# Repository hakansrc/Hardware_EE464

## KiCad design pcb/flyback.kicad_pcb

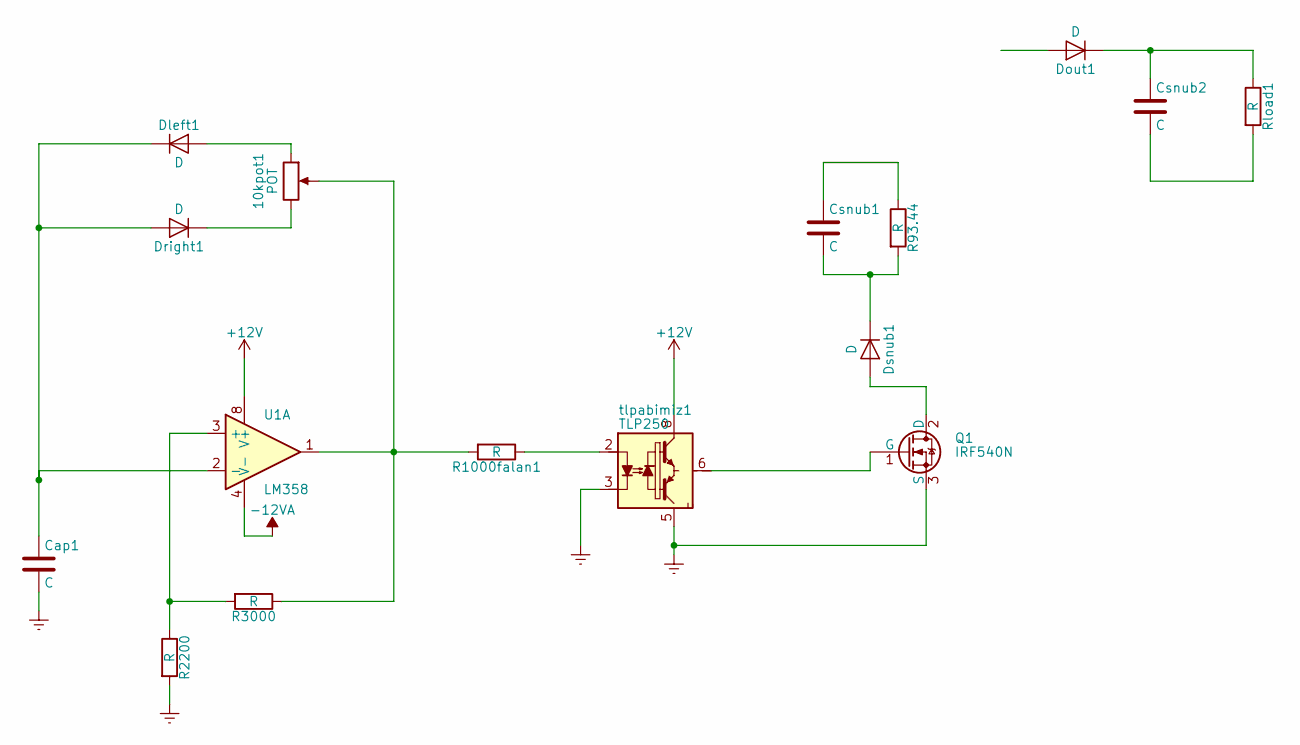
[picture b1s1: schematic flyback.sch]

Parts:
10kpot1: POT; Potentiometer_Alps_RK163_Single_Vertical
Cap1: C; C_Rect_L9.0mm_W2.5mm_P7.50mm_MKT
Csnub1: C; CP_Radial_D7.5mm_P2.50mm
Csnub2: C; CP_Radial_D26.0mm_P10.00mm_SnapIn
Dleft1: D; D_DO-201AD_P12.70mm_Horizontal
Dout1: D; D_5KPW_P12.70mm_Horizontal
Dright1: D; D_DO-201AD_P12.70mm_Horizontal
Dsnub1: D; D_A-405_P12.70mm_Horizontal
Q1: IRF540N; TO-220-3_Vertical
R93.44: R; R_Axial_Power_L38.0mm_W9.0mm_P45.72mm
R1000falan1, R2200, R3000: R; R_Axial_DIN0414_L11.9mm_D4.5mm_P15.24mm_Horizontal
Rload1: R; R_Axial_DIN0414_L11.9mm_D4.5mm_P15.24mm_Horizontal
U1: LM358; DIP-8_W8.89mm_SMDSocket_LongPads
tlpabimiz1: TLP250; DIP-8_W8.89mm_SMDSocket_LongPads

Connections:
+12V: U1.8 (V+), tlpabimiz1.8 (VCC)
-12VA: U1.4 (V-)
Earth: Cap1.2, Q1.3 (S), R2200.2, tlpabimiz1.3 (C), tlpabimiz1.5 (VEE)
unnamed: 10kpot1.1, Dleft1.2 (A)
unnamed: 10kpot1.2, R1000falan1.2, R3000.1, U1.1
unnamed: 10kpot1.3, Dright1.1 (K)
unnamed: Cap1.1, Dleft1.1 (K), Dright1.2 (A), U1.2 (-)
unnamed: Csnub1.1, R93.44.1
unnamed: Csnub1.2, Dsnub1.1 (K), R93.44.2
unnamed: Csnub2.1, Dout1.1 (K), Rload1.1
unnamed: Csnub2.2, Rload1.2
unnamed: Dsnub1.2 (A), Q1.2 (D)
unnamed: Q1.1 (G), tlpabimiz1.6 (VO), tlpabimiz1.7 (VO)
unnamed: R1000falan1.1, tlpabimiz1.2 (A)
unnamed: R2200.1, R3000.2, U1.3 (+)

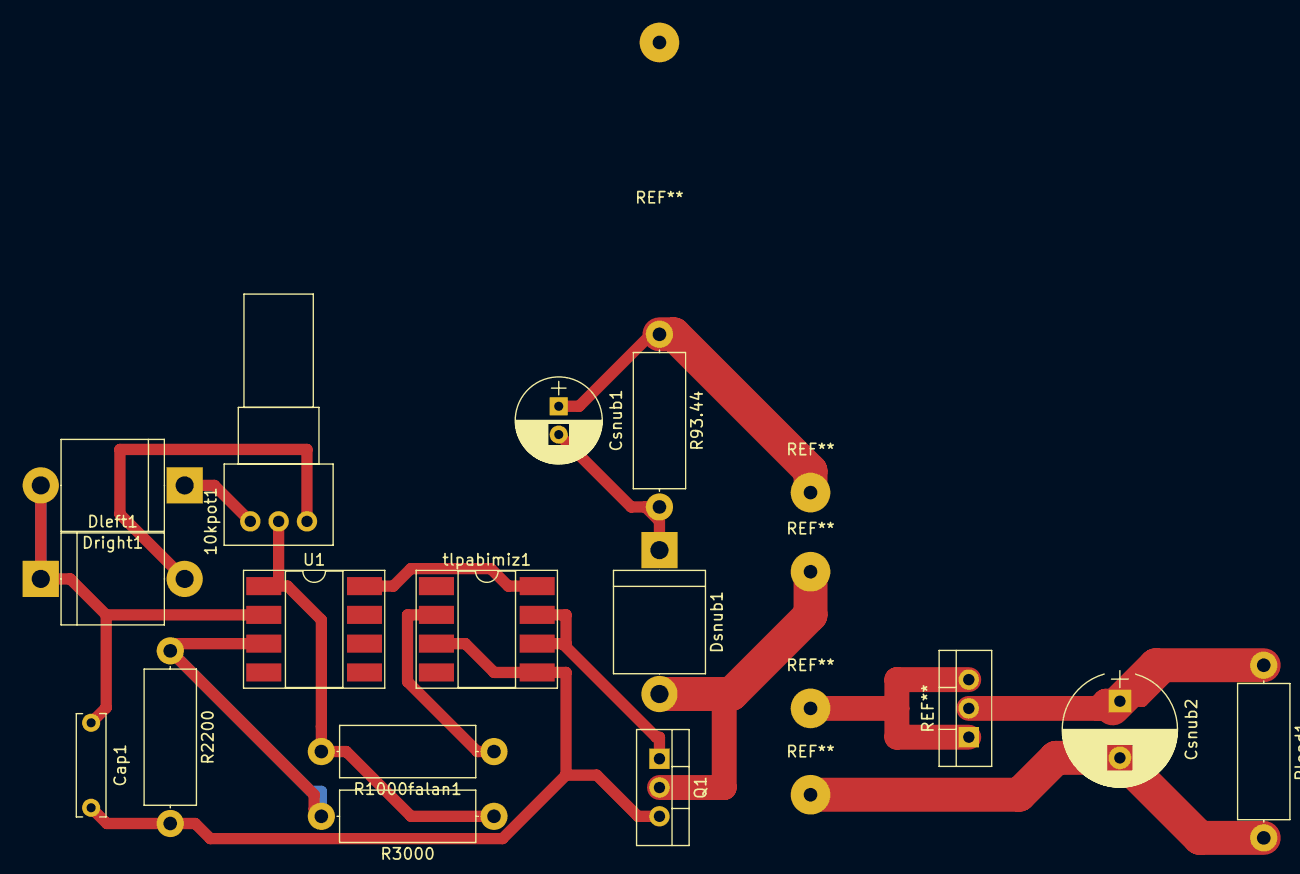
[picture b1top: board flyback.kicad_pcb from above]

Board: 2 copper layers, 15 parts (0 on the bottom side), 14 nets.

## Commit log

2018-04-11 preparation for part a
2018-04-13 transformer design beginning
2018-04-16 second version of q1
2018-04-16 core selection for the flyback
    https://www.digikey.com/product-detail/en/epcos-tdk/B65813J0250A041/495-5276-ND/3914229
2018-04-17 Buck Transfer Function for on period
2018-04-17 Off state and A B C matrices
2018-04-17 first draft of the report with introduction
2018-04-17 simulation for question-2 converter
2018-04-17 capacitor calculation, different core is selected
    https://www.digikey.com/product-detail/en/epcos-tdk/B65887E0160A041/495-5332-ND/3914482
2018-04-18 syncing
2018-04-18 Buck Matrices in Word
2018-04-18 Transfer Function is obtained analytically.
2018-04-18 simulation of question 2 with psim and bode plot
2018-04-18 2.a is almost done
    Some comments will be added.
2018-04-18 2b Bode Plot PSIM result
2018-04-19 moving on with the report, q1 almost finished
2018-04-19 simulation file for question 2 and results of question 2 for the report
2018-04-19 input step change
2018-04-20 Q2 parta added to report
2018-04-20 2c-d completed
2018-04-20 sync
2018-04-20 Q1 and conclusion is done
2018-04-20 typos
2018-04-20 Part2 report,
    some comments are missing
2018-04-20 last version of part2
2018-04-20 final version of the report
2018-04-24 core drawings
2018-04-24 transformer design for the new core
2018-05-10 integrator olayarı and pcb design a giriş
2018-06-02 new snubber
